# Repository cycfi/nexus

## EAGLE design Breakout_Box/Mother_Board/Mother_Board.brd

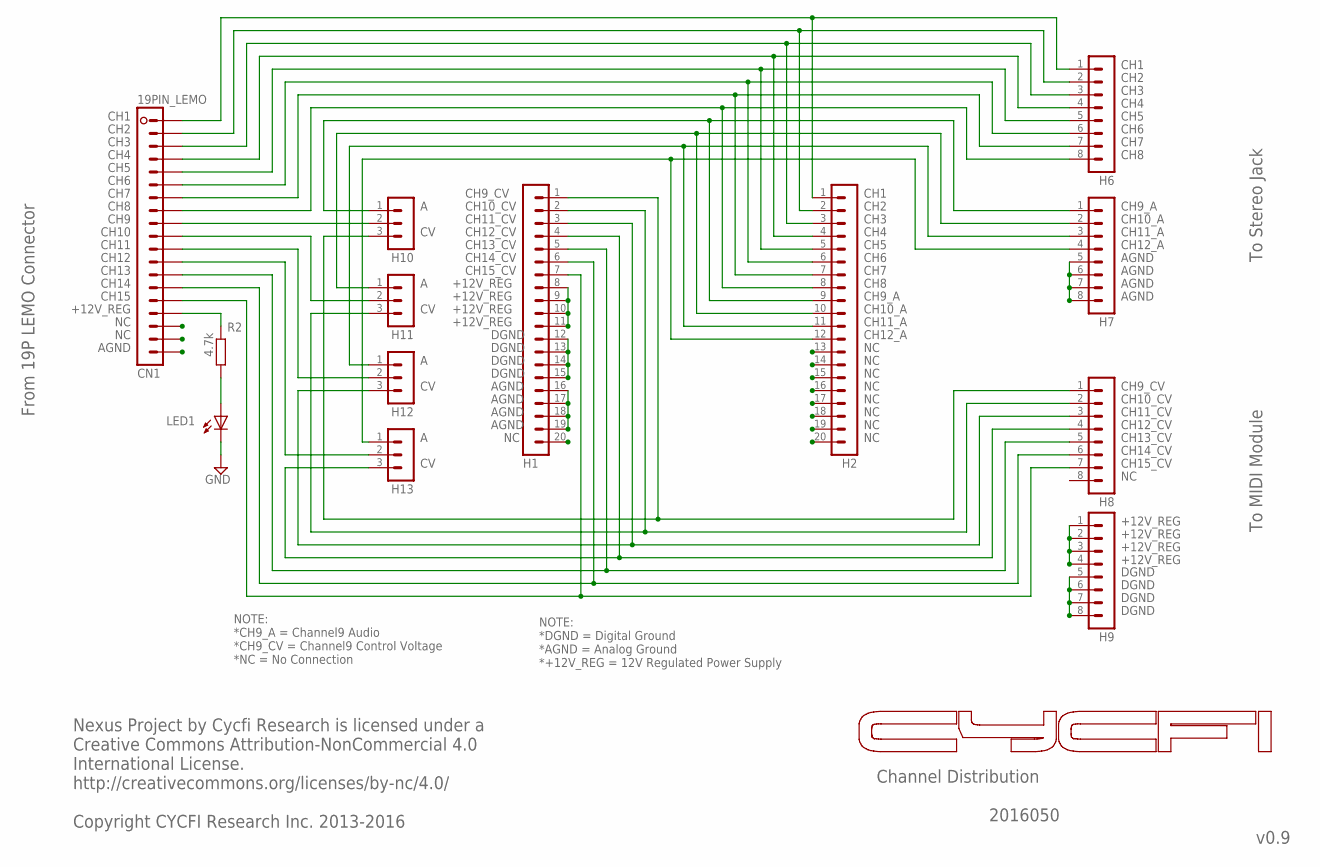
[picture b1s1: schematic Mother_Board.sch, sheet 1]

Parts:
CN1: 19PIN_LEMO
H1, H2: MA20-1
H6, H7, H8, H9: MA08-1
H10, H11, H12, H13: MA03-1_EDITED; MA03-1_
LED1: LED3MM
R2: 4.7k; R0402

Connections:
+12V_REG: CN1.P$16 (16), H1.8, H1.9, H1.10, H1.11, H9.1, H9.2, H9.3, H9.4, R2.1; also elsewhere on the board
AGND: CN1.P$19 (19), H1.16, H1.17, H1.18, H1.19, H7.5, H7.6, H7.7, H7.8, LED1.K (C); also elsewhere on the board
DGND: H1.12, H1.13, H1.14, H1.15, H9.5, H9.6, H9.7, H9.8
unnamed: CN1.P$1 (1), H2.1, H6.1
unnamed: CN1.P$2 (2), H2.2, H6.2
unnamed: CN1.P$3 (3), H2.3, H6.3
unnamed: CN1.P$4 (4), H2.4, H6.4
unnamed: CN1.P$5 (5), H2.5, H6.5
unnamed: CN1.P$6 (6), H2.6, H6.6
unnamed: CN1.P$7 (7), H2.7, H6.7
unnamed: CN1.P$8 (8), H2.8, H6.8
unnamed: CN1.P$9 (9), H10.2
unnamed: CN1.P$10 (10), H11.2
unnamed: CN1.P$11 (11), H12.2
unnamed: CN1.P$12 (12), H13.2
unnamed: H2.10, H7.2, H11.1
unnamed: LED1.A, R2.2
unnamed: H2.12, H7.4, H13.1
unnamed: H2.11, H7.3, H12.1
unnamed: H2.9, H7.1, H10.1
unnamed: H1.1, H8.1, H10.3
unnamed: H1.2, H8.2, H11.3
unnamed: H1.3, H8.3, H12.3
unnamed: H1.4, H8.4, H13.3
unnamed: CN1.P$13 (13), H1.5, H8.5
unnamed: CN1.P$14 (14), H1.6, H8.6
unnamed: CN1.P$15 (15), H1.7, H8.7

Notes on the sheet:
Channel Distribution
v0.9
2016050
CH1
CH2
CH3
CH4
CH5
CH6
CH7
CH8
CH9_A
CH10_A
CH11_A
CH12_A
CH9_CV
CH10_CV
CH11_CV
CH12_CV
CH13_CV
CH14_CV
CH15_CV
AGND
From 19P LEMO Connector
To Stereo Jack
To MIDI Module
NOTE: *DGND = Digital Ground *AGND = Analog Ground *+12V_REG = 12V Regulated Power Supply
NOTE: *CH9_A = Channel9 Audio *CH9_CV = Channel9 Control Voltage *NC = No Connection
DGND
Nexus Project by Cycfi Research is licensed under a Creative Commons Attribution-NonCommercial 4.0 International License. http://creativecommons.org/licenses/by-nc/4.0/ Copyright CYCFI Research Inc. 2013-2016
CH9
CH10
CH11
CH12
CH13
CH14
CH15

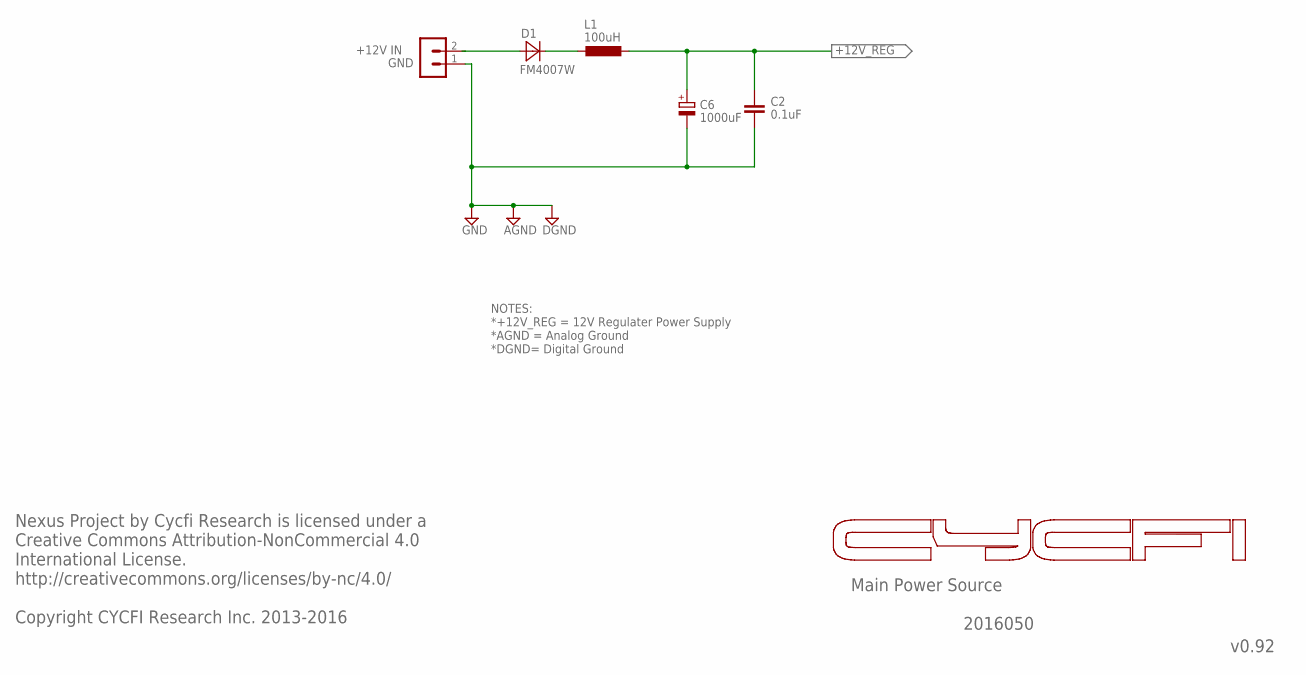
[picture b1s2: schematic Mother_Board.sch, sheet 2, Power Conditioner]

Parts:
C2: 0.1uF; C0603
C6: 1000uF; 140CLH-1010
D1: FM4007W; SMX
H14: MA02-1
L1: 100uH; L1280

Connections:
+12V_REG: C2.1, C6.+, L1.P$2 (2); also elsewhere on the board
AGND: C2.2, C6.-, H14.1; also elsewhere on the board
unnamed: D1.ANODE (A), H14.2
unnamed: D1.CATHODE (C), L1.P$1 (1)

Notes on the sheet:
Main Power Source
NOTES: *+12V_REG = 12V Regulater Power Supply *AGND = Analog Ground *DGND= Digital Ground
v0.92
+12V IN
GND
Nexus Project by Cycfi Research is licensed under a Creative Commons Attribution-NonCommercial 4.0 International License. http://creativecommons.org/licenses/by-nc/4.0/ Copyright CYCFI Research Inc. 2013-2016
2016050

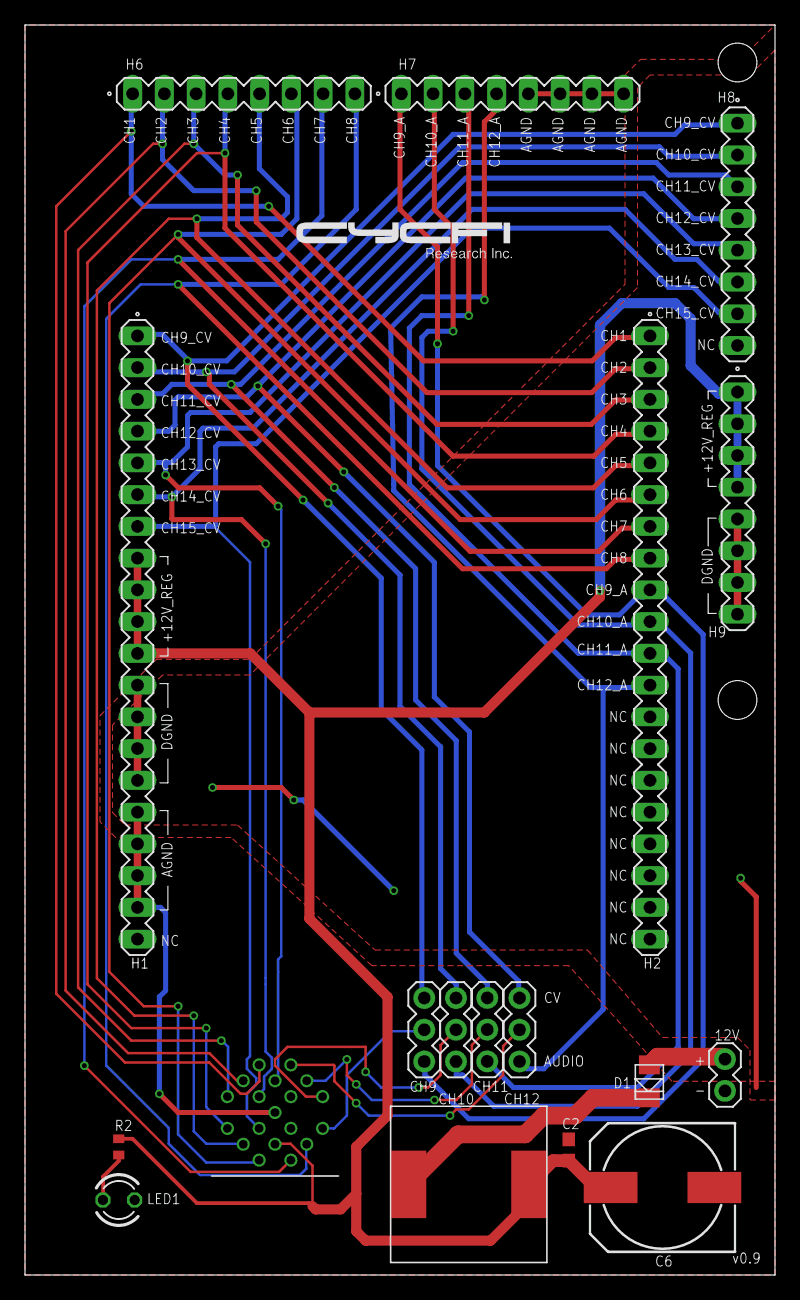
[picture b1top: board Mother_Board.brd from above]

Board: 2 copper layers, 60.0 x 100.0 mm, 18 parts (0 on the bottom side), 29 nets.

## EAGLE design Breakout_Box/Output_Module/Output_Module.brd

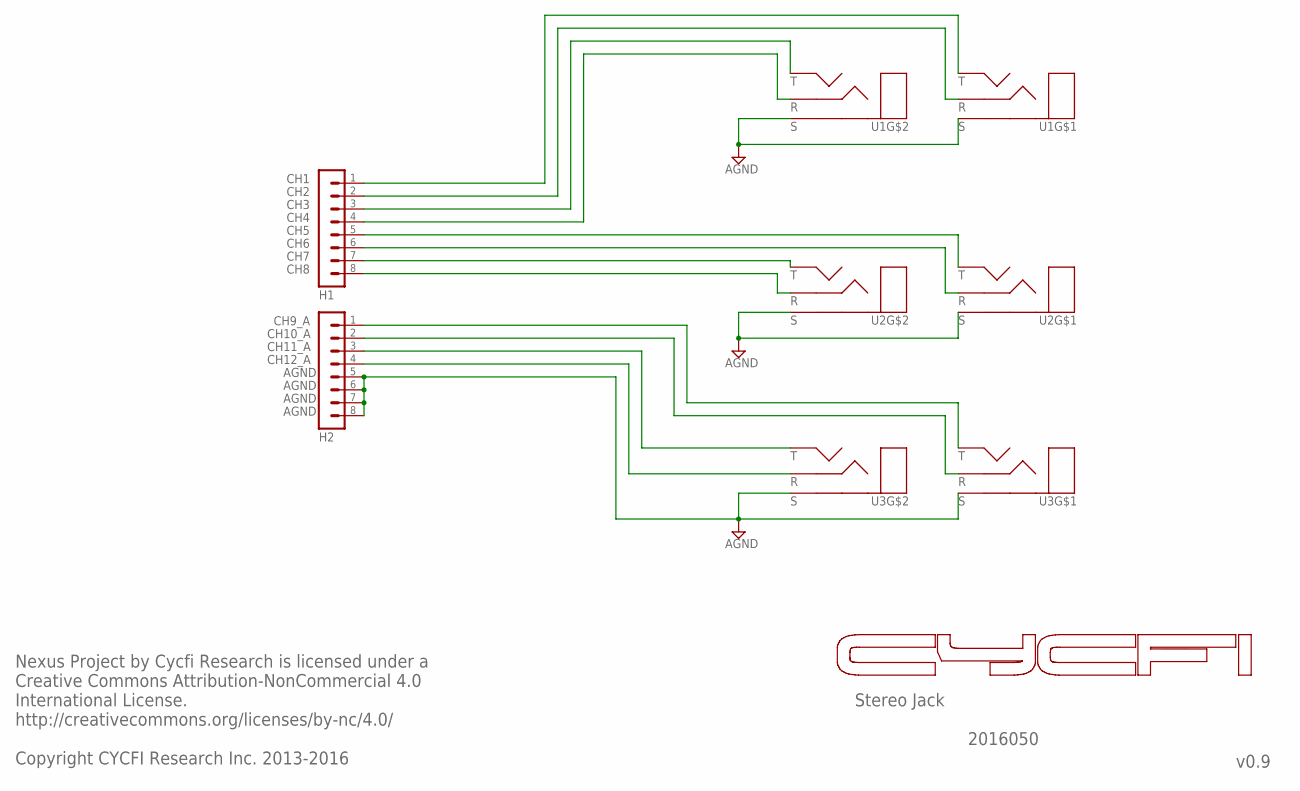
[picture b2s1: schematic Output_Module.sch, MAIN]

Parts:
H1, H2: MA08-1
U1, U2, U3: AGND; NSJ12HC

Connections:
AGND: H2.5, H2.6, H2.7, H2.8, U1.G (DGND), U1.SB (S), U1.ST (S), U2.G (DGND), U2.SB (S), U2.ST (S), U3.G (DGND), U3.SB (S), U3.ST (S)
unnamed: H1.1, U1.TT (T)
unnamed: H1.2, U1.RT (R)
unnamed: H1.3, U1.TB (T)
unnamed: H1.4, U1.RB (R)
unnamed: H1.5, U2.TT (T)
unnamed: H1.6, U2.RT (R)
unnamed: H1.7, U2.TB (T)
unnamed: H1.8, U2.RB (R)
unnamed: H2.1, U3.TT (T)
unnamed: H2.2, U3.RT (R)
unnamed: H2.3, U3.TB (T)
unnamed: H2.4, U3.RB (R)

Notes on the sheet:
Stereo Jack
v0.9
Nexus Project by Cycfi Research is licensed under a Creative Commons Attribution-NonCommercial 4.0 International License. http://creativecommons.org/licenses/by-nc/4.0/ Copyright CYCFI Research Inc. 2013-2016
2016050
CH1
CH2
CH3
CH4
CH5
CH6
CH7
CH8
CH9_A
CH10_A
CH11_A
CH12_A

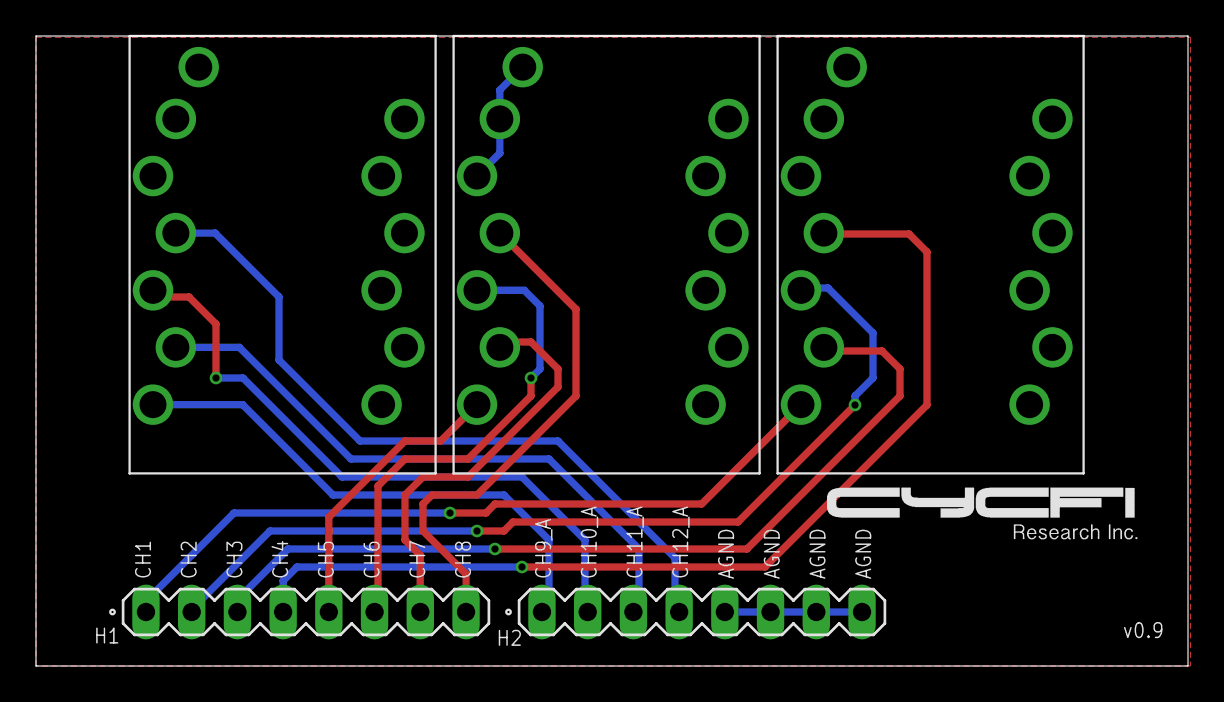
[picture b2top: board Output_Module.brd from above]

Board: 2 copper layers, 64.0 x 35.0 mm, 5 parts (0 on the bottom side), 13 nets.

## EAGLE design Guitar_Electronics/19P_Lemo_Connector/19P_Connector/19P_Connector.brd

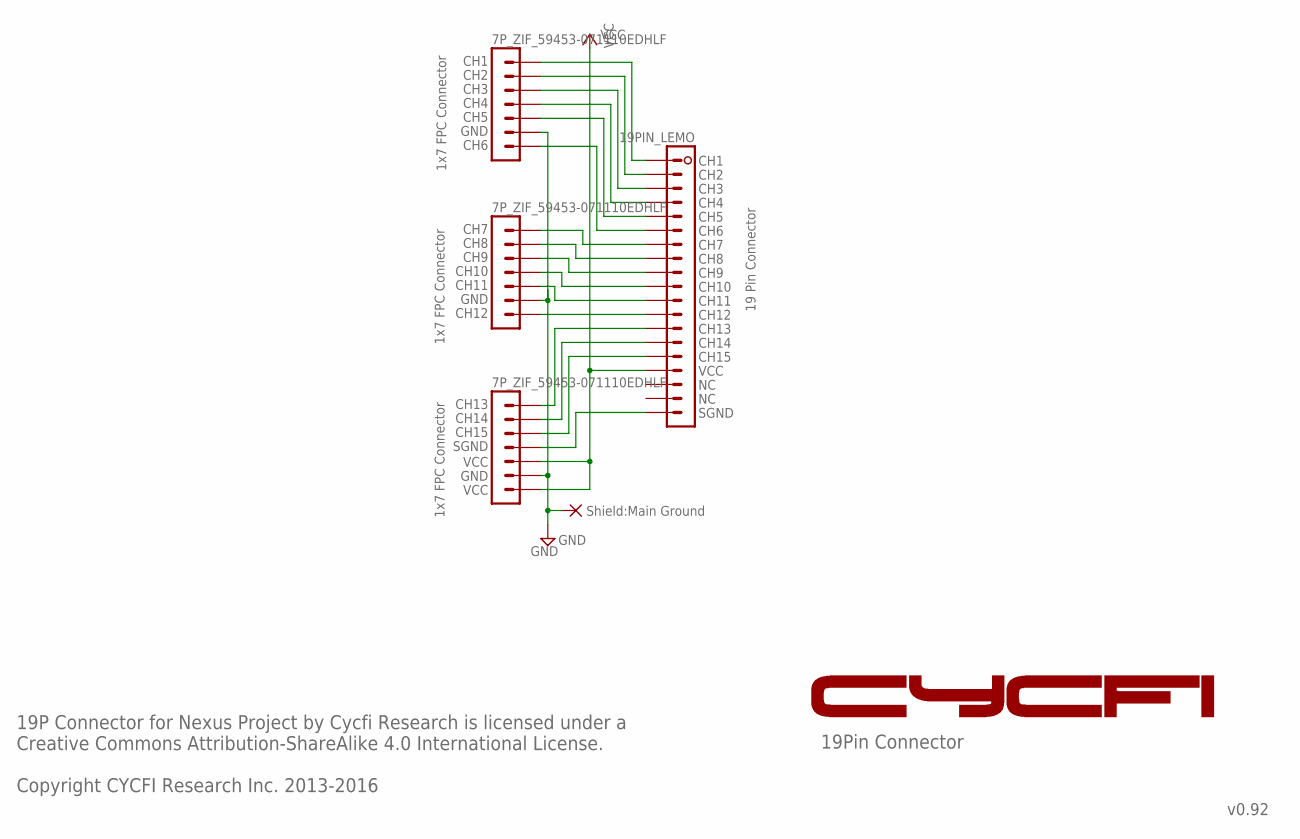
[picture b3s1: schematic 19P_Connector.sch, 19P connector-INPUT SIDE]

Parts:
C1: 19PIN_LEMO
H1, H2, H3: 7P_ZIF_59453-071110EDHLF
PAD1: 1,6/0,8

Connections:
CH1: C1.P$1 (1), H1.P$1 (1)
CH2: C1.P$2 (2), H1.P$2 (2)
CH3: C1.P$3 (3), H1.P$3 (3)
CH4: C1.P$4 (4), H1.P$4 (4)
CH5: C1.P$5 (5), H1.P$5 (5)
CH6: C1.P$6 (6), H1.P$7 (7)
CH7: C1.P$7 (7), H2.P$1 (1)
CH8: C1.P$8 (8), H2.P$2 (2)
CH9: C1.P$9 (9), H2.P$3 (3)
CH10: C1.P$10 (10), H2.P$4 (4)
CH11: C1.P$11 (11), H2.P$5 (5)
CH12: C1.P$12 (12), H2.P$7 (7)
CH13: C1.P$13 (13), H3.P$1 (1)
CH14: C1.P$14 (14), H3.P$2 (2)
CH15: C1.P$15 (15), H3.P$3 (3)
GND: H1.P$6 (6), H2.P$6 (6), H3.P$6 (6), PAD1.1
unnamed: C1.P$19 (19), H3.P$4 (4)
VCC: C1.P$16 (16), H3.P$5 (5), H3.P$7 (7)

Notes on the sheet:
CH1
CH2
CH3
CH4
CH5
CH6
CH7
CH8
CH9
CH10
CH11
CH12
CH13
CH14
CH15
VCC
SGND
GND
Shield:Main Ground
1x7 FPC Connector
19 Pin Connector
19Pin Connector
v0.92
19P Connector for Nexus Project by Cycfi Research is licensed under a Creative Commons Attribution-ShareAlike 4.0 International License. Copyright CYCFI Research Inc. 2013-2016

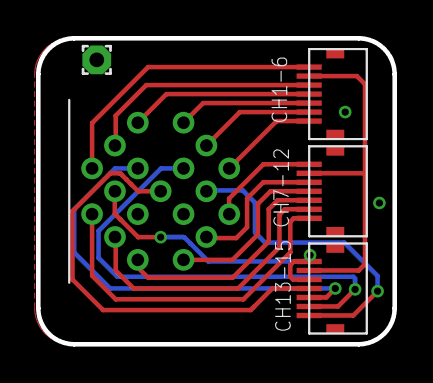
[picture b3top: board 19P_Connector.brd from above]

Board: 2 copper layers, 19.8 x 17.0 mm, 5 parts (0 on the bottom side), 18 nets.

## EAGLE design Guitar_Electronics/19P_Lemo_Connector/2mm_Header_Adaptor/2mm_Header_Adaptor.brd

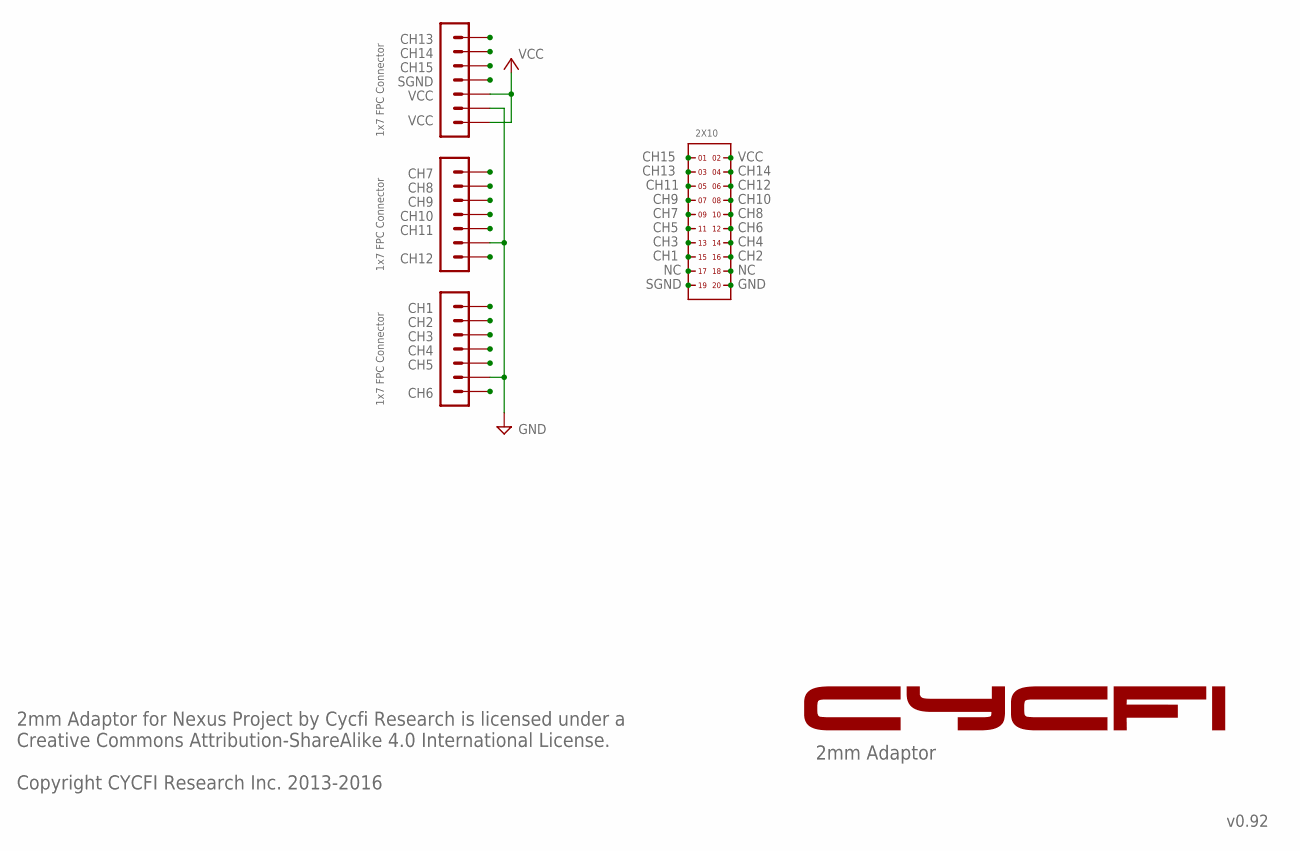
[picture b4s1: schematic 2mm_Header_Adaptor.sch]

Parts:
H1, H2, H3: 7P_ZIF_59453-071110EDHLF
H4: 2X10

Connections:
CH1: H1.P$7 (7), H4.15
CH2: H1.P$6 (6), H4.16
CH3: H1.P$5 (5), H4.13
CH4: H1.P$4 (4), H4.14
CH5: H1.P$3 (3), H4.11
CH6: H1.P$1 (1), H4.12
CH7: H2.P$7 (7), H4.9
CH8: H2.P$6 (6), H4.10
CH9: H2.P$5 (5), H4.7
CH10: H2.P$4 (4), H4.8
CH11: H2.P$3 (3), H4.5
CH12: H2.P$1 (1), H4.6
GND: H1.P$2 (2), H2.P$2 (2), H3.P$2 (2), H4.20
MIDI1: H3.P$7 (7), H4.3
MIDI2: H3.P$6 (6), H4.4
MIDI3: H3.P$5 (5), H4.1
NC1: H4.17
NC2: H4.18
VCC: H3.P$1 (1), H3.P$3 (3), H4.2
VGND: H3.P$4 (4), H4.19

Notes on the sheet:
CH6
CH5
CH4
CH3
CH2
CH1
CH12
CH11
CH10
CH9
CH8
CH7
GND
CH14
VCC
SGND
CH13
CH15
2mm Adaptor
v0.92
1x7 FPC Connector
2mm Adaptor for Nexus Project by Cycfi Research is licensed under a Creative Commons Attribution-ShareAlike 4.0 International License. Copyright CYCFI Research Inc. 2013-2016

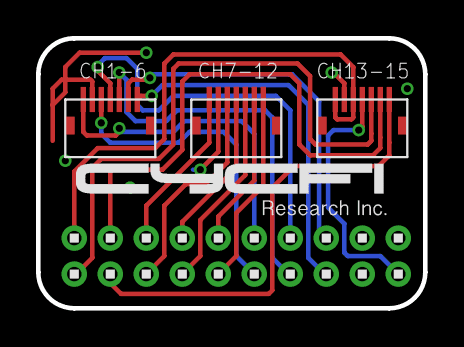
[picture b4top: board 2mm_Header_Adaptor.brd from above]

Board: 2 copper layers, 21.5 x 15.0 mm, 4 parts (0 on the bottom side), 18 nets.

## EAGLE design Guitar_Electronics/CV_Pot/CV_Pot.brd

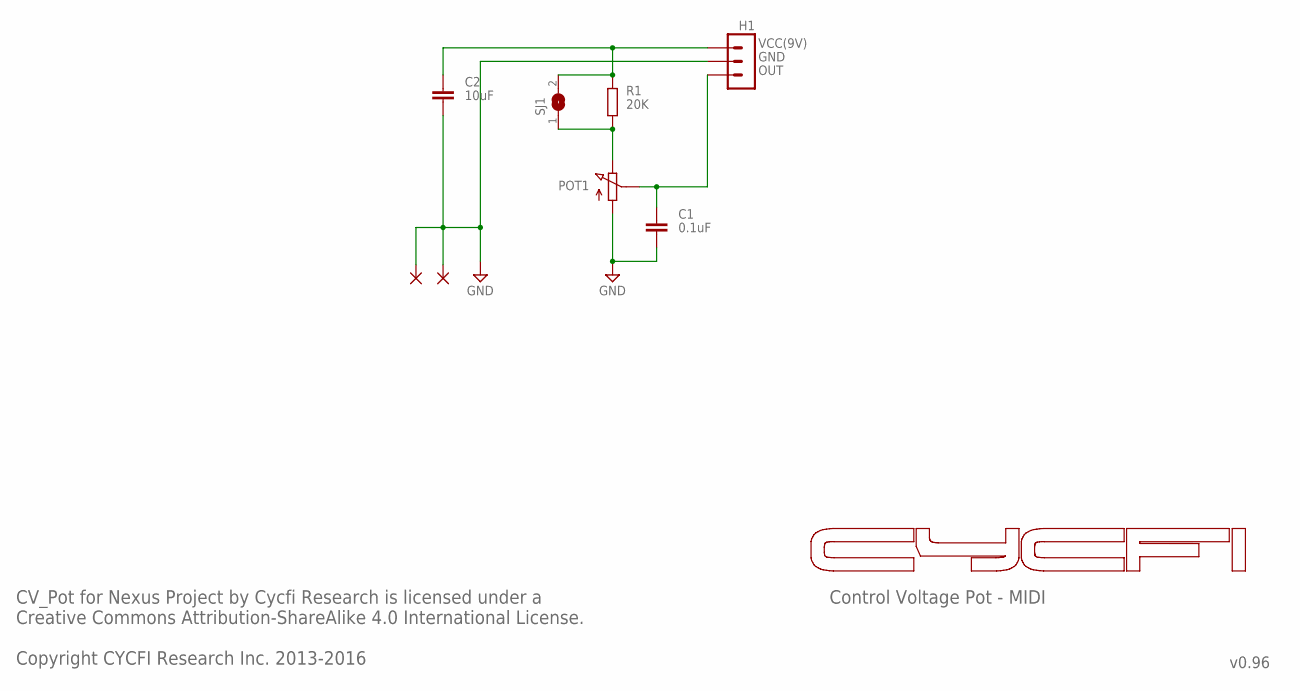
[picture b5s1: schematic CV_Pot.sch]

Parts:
C1: 0.1uF; C0603
C2: 10uF; C0805
GND1, GND2: SMD2; SMD1,27-2,54
H1: 3PIN-SMD-2.54MM; 3P-SMD-2.54MM
POT1: 25K; POT_EU_PDB181GTR
R1: 20K; R0402
SJ1: SJ

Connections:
GND: C1.2, C2.2, GND1.1, GND2.1, H1.P$2 (2), POT1.A1 (1)
unnamed: C2.1, H1.P$3 (3), R1.2, SJ1.2
unnamed: POT1.A3 (3), R1.1, SJ1.1
OUT: C1.1, H1.P$1 (1), POT1.A2 (2)

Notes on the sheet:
Control Voltage Pot - MIDI
VCC(9V)
GND
OUT
v0.96
CV_Pot for Nexus Project by Cycfi Research is licensed under a Creative Commons Attribution-ShareAlike 4.0 International License. Copyright CYCFI Research Inc. 2013-2016

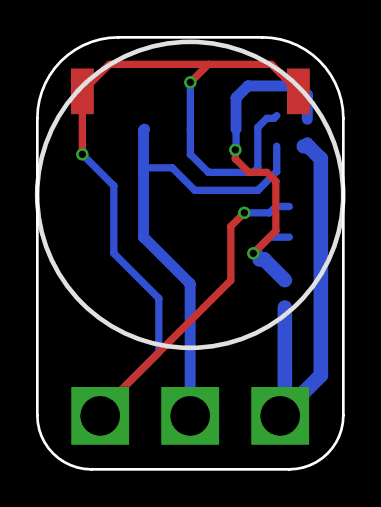
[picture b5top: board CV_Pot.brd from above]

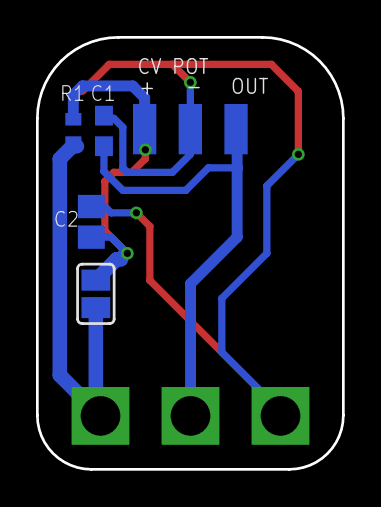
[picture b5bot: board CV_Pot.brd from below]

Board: 2 copper layers, 17.0 x 24.0 mm, 8 parts (5 on the bottom side), 4 nets.

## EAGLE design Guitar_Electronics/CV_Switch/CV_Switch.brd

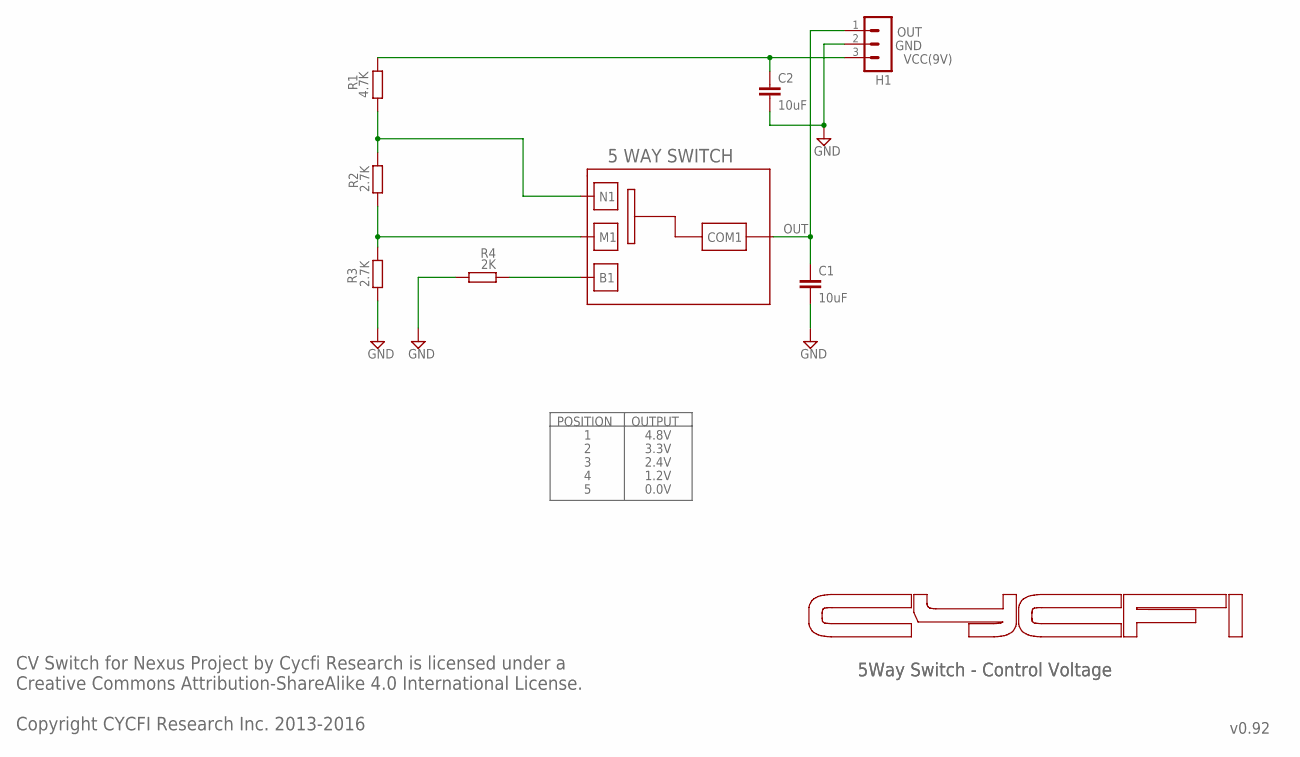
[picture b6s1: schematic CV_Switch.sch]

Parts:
C1, C2: 10uF; C0805
H1: MA03-1_EDITED; MA03-1_
R1: 4.7K; R0402
R2, R3: 2.7K; R0402
R4: 2K; R0402
U$1: 5WAY_SW_1; 5WAY_SW_CASTELLATED

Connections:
GND: C1.2, C2.2, H1.2, R3.1, R4.1
unnamed: C2.1, H1.3, R1.2
unnamed: R1.1, R2.2, U$1.N1
unnamed: R4.2, U$1.B1
unnamed: R2.1, R3.2, U$1.M1
OUT: C1.1, H1.1, U$1.COM1

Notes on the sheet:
VCC(9V)
GND
OUT
5Way Switch - Control Voltage
v0.92
CV Switch for Nexus Project by Cycfi Research is licensed under a Creative Commons Attribution-ShareAlike 4.0 International License. Copyright CYCFI Research Inc. 2013-2016
POSITION
OUTPUT
4.8V
3.3V
2.4V
1.2V
0.0V

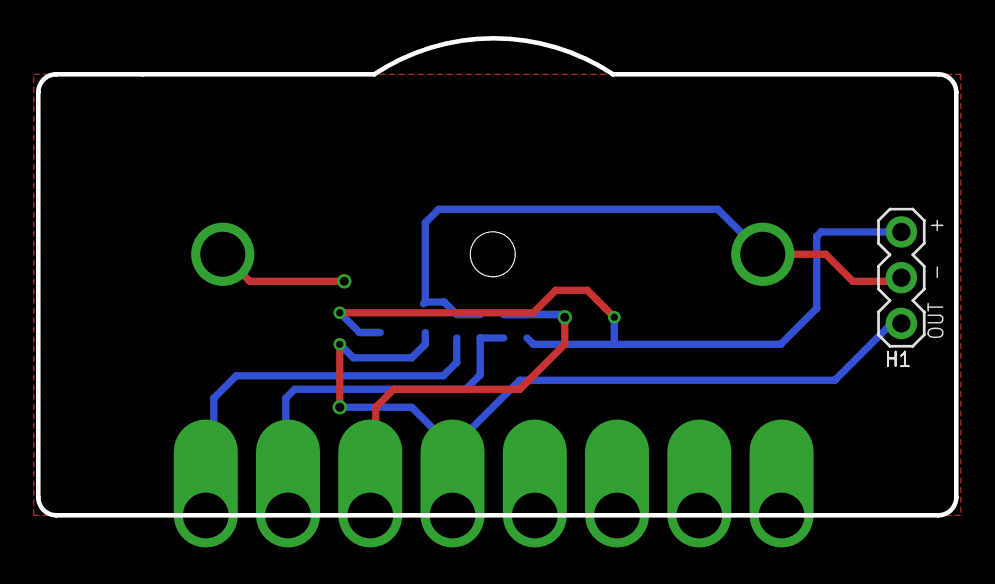
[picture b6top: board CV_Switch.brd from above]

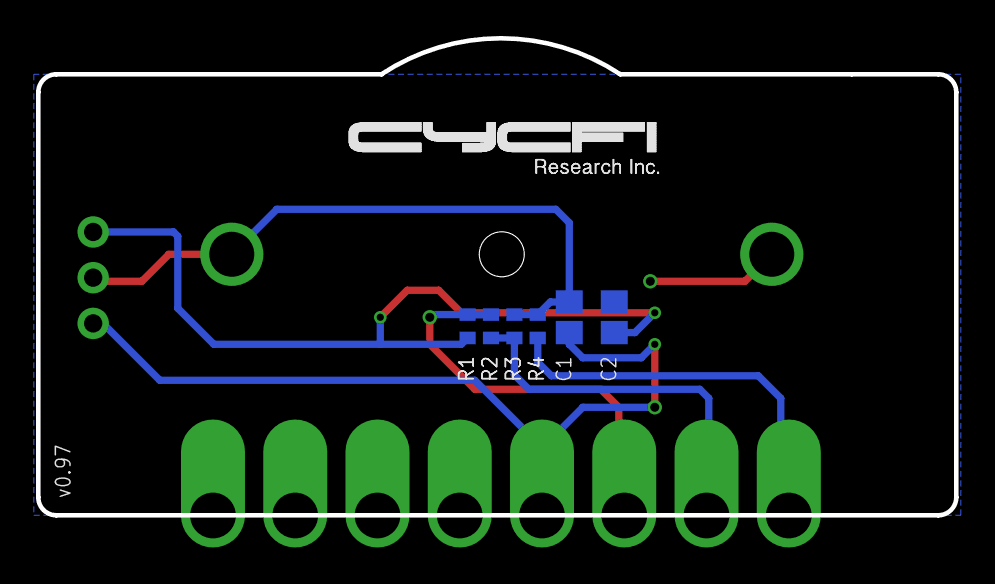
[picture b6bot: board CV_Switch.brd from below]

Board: 2 copper layers, 51.0 x 26.5 mm, 8 parts (6 on the bottom side), 6 nets.
